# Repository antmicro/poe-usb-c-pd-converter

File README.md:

# Power over Ethernet to USB-C Power Delivery Adapter 

Copyright (c) 2024-2025 [Antmicro](https://www.antmicro.com)

## Overview

This project contains open hardware PCB design files for an adapter that splits a Power-over-Ethernet (PoE) capable RJ45 interface port into a USB-C Power Delivery (PD) port and an Ethernet RJ45 port. 
It negotiates power from PoE Power Sourcing Equipment (PSE) such as a PoE switch or a PoE injector.
For the USB-C connection, the board serves as an Upstream Facing Port (UFP) power source.
The USB-C port can be used for reading current and voltage negotiated for the PD.

## Key features

* RJ45 input port for data and PoE++ (IEEE 802.3bt)
* RJ45 output port passing raw Ethernet data from the input port
* USB-C regular connector with Power Delivery feature and USB data downstream
* Automatic input power negotiation (up to 71W) from PSE
* Externally programmable flash memory
* Programmable USB Power Delivery power profiles up to 60W
* On-board VBUS voltage, current and power measurement circuitry
* On-board external fan driver with a 4-pin standard receptacle
* 112 x 56 mm (4.4 x 2.2 inch) mechanical outline

## Project structure

The main directory contains KiCad PCB design files, a LICENSE and a README.
The remaining files are stored in the following directories:
* `img` - contains graphics for this README

## License
 
This project is published under the [Apache-2.0](LICENSE) license.

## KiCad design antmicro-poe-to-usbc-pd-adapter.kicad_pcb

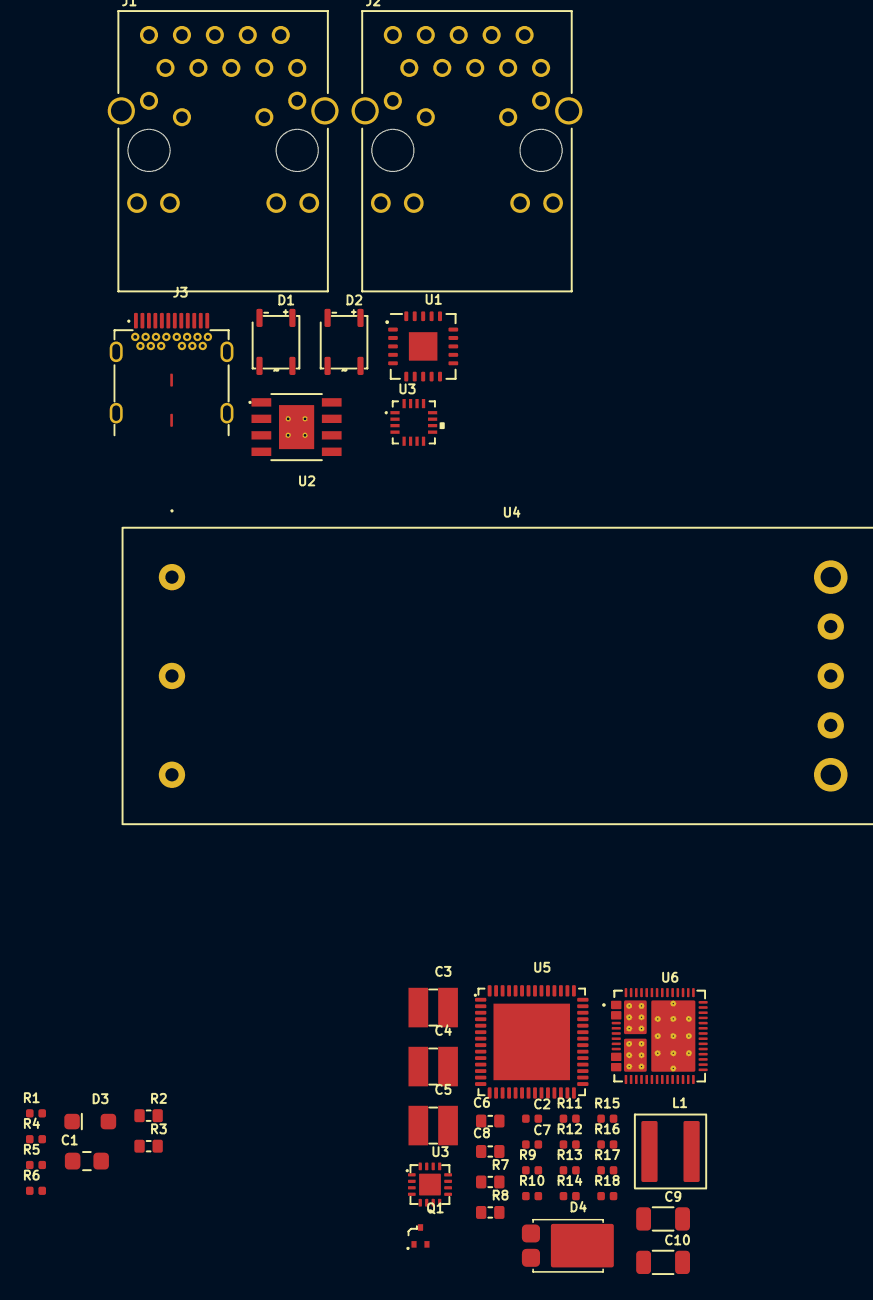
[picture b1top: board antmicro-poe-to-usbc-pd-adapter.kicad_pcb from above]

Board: 2 copper layers, 44 parts (0 on the bottom side), 49 nets, no tracks yet.

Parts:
C1: C_100n_100V_0805; C_0805_2012Metric
C2: C_10n_50V_X7R_0402; C_0402_1005Metric
C3: C_4u7_1210_100V; C_1210_3225Metric
C4, C5: C_2u2_1210; C_1210_3225Metric
C6, C8: C_100n_100V_X7R_0603; C_0603_1608Metric
C7: C_3n3_0402; C_0402_1005Metric
C9, C10: C_47u_25V_1206; C_1206_3216Metric
D1, D2: CD-MMBL110S; DFN3538
D3: PTVS58VS1UR,115; D_SOD-123F
D4: PDS760; PowerDI5
J1, J2: Bus_RJ45_5-2337992-8; RJ45_X-2337992-8_Horizontal
J3: USB-C_WE_632723300011; USB-C_Receptacle_WE_632723300011
L1: L_6u8_6.1A_MPS-MPL-AL5050; L_MPS-MPL-AL5050
Q1: PJE138K; SOT-523
R1: R_24k9_0402; R_0402_1005Metric
R2: R_63R4_0603; R_0603_1608Metric
R3: R_90R9_0603; R_0603_1608Metric
R4: R_1k3_0402; R_0402_1005Metric
R5: R_0R_0402; R_0402_1005Metric
R6: R_49k9_0402; R_0402_1005Metric
R7, R8: R_0R_0603; R_0603_1608Metric
R9: R_27k_0402; R_0402_1005Metric
R10: R_470k_0402; R_0402_1005Metric
R11: R_100k_0402; R_0402_1005Metric
R12: R_10k_0402; R_0402_1005Metric
R13: R_200k_0402; R_0402_1005Metric
R14: R_7k68_0402; R_0402_1005Metric
R15, R16: R_2k7_0402; R_0402_1005Metric
R17: R_4k7_0402; R_0402_1005Metric
R18: R_17k4_0402; R_0402_1005Metric
U1: TPS2372-3RGWR; VQFN-20_5x5x1mm_P0.65mm
U2: LV14540DDAR; SOIC-8-1EP_3.9x4.9x1.75mm_P1.27mm_EP_vias
U3: INA230AIRGTR; VQFN-16-1EP_3x3mm_P0.5mm_EP1.68x1.68mm
U3#2: STUSB4710AQ1TR; QFN-16_3x3mm_P0.5mm
U4: IEA48003A280V-001-R
U5: FT4232H_VQFN; QFN-56-1EP_8x8mm_P0.5mm
U6: TPS65988DHRSHR; IC_TPS65987DDHRSHR

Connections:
/CLSA: R2.2, U1.3 (CLSA)
/CLSB: R3.2, U1.6 (CLSB)
/P1: J1.1, J2.1
/P2: J1.2, J2.2
/P3: J1.3, J2.3
/P4: J1.4, J2.4
/P5: J1.5, J2.5
/P6: J1.6, J2.6
/P7: J1.7, J2.7
/P8: J1.8, J2.8
/P9: J1.9, J2.9
/P10: J1.10, J2.10
/POE.VC1: D1.3, J1.11 (VC1)
/POE.VC2: D1.4, J1.12 (VC2)
/POE.VC3: D2.4, J1.13 (VC3)
/POE.VC4: D2.3, J1.14 (VC4)
/VDD: C1.2, D1.2, D2.2, R1.1, R10.2, U1.1 (VDD), U4.1 (VIN+)
/VSS: C1.1, D1.1, D2.1, R2.1, R3.1, R4.1, R5.2, R6.1, U1.4 (VSSA), U1.5 (VSSB)
GND: C2.1, C3.1, C4.1, C5.1, C6.1, C7.1, C9.1, C10.1, D4.2 (A), R8.1, R9.1, R18.1, U2.7 (GND), U2.9 (GND), U4.4 (VOUT-), U4.5 (SENSE-)
GNDD: Q1.2 (S), R11.1, U1.11 (RTNA), U1.12 (RTNB), U4.3 (VIN-)
unnamed: C9.2, C10.2, L1.2, R13.2
unnamed: C8.1, D4.1 (C), L1.1, U2.8 (SW)
unnamed: J1.19 (SHIELD), J1.20 (SHIELD)
unnamed: J2.19 (SHIELD), J2.20 (SHIELD)
unnamed: J3.A1 (GND), J3.A12 (GND), J3.B1 (GND), J3.B12 (GND)
unnamed: Q1.3 (D), U4.2 (!ON)
unnamed: Q1.1 (G), R10.1, R11.2, R12.1
unnamed: R14.1, R15.2
unnamed: R15.1, R16.2
unnamed: R16.1, R17.2
unnamed: R17.1, R18.2
unnamed: R4.2, U1.8 (AMPS_CTL)
unnamed: R1.2, U1.2 (DEN)
unnamed: R5.1, U1.9 (MPS_DUTY)
unnamed: R12.2, U1.13 (PG)
unnamed: R6.2, U1.7 (REF)
unnamed: C8.2, U2.1 (BOOT)
unnamed: C3.2, C4.2, C5.2, C6.2, R7.1, U2.2 (VIN), U2.3 (EN), U4.7 (SENSE+), U4.8 (VOUT+)
unnamed: R13.1, R14.2, U2.5 (FB)
unnamed: R9.2, U2.4 (RT)
unnamed: C7.2, U2.6 (SS)
unnamed: C2.2, R7.2, R8.2, U4.6 (TRIM)
unnamed: U5.21 (GND), U5.41 (GND), U5.45 (GND), U5.57 (GND)
unnamed: U5.16 (V_{CCIO}), U5.36 (V_{CCIO}), U5.50 (V_{CCIO})
unnamed: U5.2 (V_{CORE}), U5.31 (V_{CORE})
unnamed: U6.20 (GND), U6.51 (GND)
unnamed: U6.8 (DRAIN1), U6.15 (DRAIN1), U6.19 (DRAIN1), U6.58 (DRAIN1)
unnamed: U6.7 (DRAIN2), U6.52 (DRAIN2), U6.56 (DRAIN2), U6.57 (DRAIN2)
VBUS: J3.A4 (VBUS), J3.A9 (VBUS), J3.B4 (VBUS), J3.B9 (VBUS)

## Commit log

2025-12-30 Add LICENSE
2025-12-30 [#62182] Connect LV14540
2025-12-30 [#62182] Create schematic place components route TPS2372
2025-12-30 [#62182] Add shunt resistor for INA230
2025-12-30 [#62623] Add planes to variable buck
2025-12-30 [#62182] Change passives, correct gnd
2025-12-30 [#62623] Improved schematic, added hierarchy
2025-12-30 [#62623] Improve schematic, change 3V3 buck inductor, correct SPI, add testpoint
2025-12-30 [#62182] Add INA230, remove STUSB4710
2025-12-30 [#62623] Las commit before major change in placement
2025-12-30 [#62182] Major changes in schematic
    Add TPS65987D
    Add FT4232H
    Add 3v3 buck
    Connect components
2025-12-30 [#62182] Update resistor fields
2025-12-30 [#62182] Place components PCB
2025-12-30 [#62623] Change hierarchy implementation
2025-12-30 [#62182] Connect INA230
    This is first commit after Meeting #62027
2025-12-30 [#62182] Update stackup
2025-12-30 [#62182] Change R5
2025-12-30 [#62623] Minor changes in placement/schematic
2025-12-30 [#62182] Tie VBUS1 and VBUS2
2025-12-30 [#62182] Add mux to flash
2025-12-30 [#62623] PCB initial placement
2025-12-30 [#62182] Add logo, add mountin holes
2025-12-30 [#62623] Minor graphical changes
2025-12-30 [#62182] Clean schematic
2025-12-30 [#62835] Route ETH differential pairs
2025-12-30 [#62835] Change dcdc placement, change IC's placement
2025-12-30 [#62835] Change R30 to geneerate CI
2025-12-30 [#62835] Start PWR plane placement
2025-12-30 [#62835] Create WRL
2025-12-30 [#62835] PoE to USB-C PD Review Rev.1.0.0 correct points 1,3,4,6,7,11
2025-12-30 [#62835] Finish routing, start silcscreen
2025-12-30 [#62835] Improve EHT tuning
2025-12-30 [#62835] Add filtering capacitors to FTDI
2025-12-30 [#62835] Add switch explanation
2025-12-30 [#62835] Add esd protection for usb, add pwr planes, route LS signals
2025-12-30 [#62835] Add 3V3 LDO
2025-12-30 [#62835] Tackle DRC problems, change vias size
2025-12-30 [#62835] Tune ETH length
2025-12-30 [#62835] Correct OSHW-logo
2025-12-30 [#62835] Add ETH receptacle diode steering
2025-12-30 [#62835] Start routing low speed signals
2025-12-30 [#62835] Add vias, second GND plane, GNDD plane, lower INA IC, minor changes
2025-12-30 [#62835] Finish silcscreen reference values placement
2025-12-30 [#62835] Tacle ERC problems, add PWR flags
2025-12-30 [#62835] Add place for SHA
2025-12-30 [#62835] Add 3V3 LDO to PCB, place CBUS capacitors, change 5V buck layout
2025-12-30 [#62835] Change L3 3V3 buck and divider, to 5V dcdc buck
2025-12-30 [#63274] Add status LEDs for PoE controller
2025-12-30 [#62835] Change IEA48003A280V-001-R input capacitors
2025-12-30 [#63274] Imported WRL, prepare for visualisation
2025-12-30 [#63274] Change sha for ########
2025-12-30 [#63274] Add heatsink, clear DRC
2025-12-30 [#62835] Change planes below IEA4800(..), place capacitors
2025-12-30 [#63274] Add testpoints, improve silcscreen
2025-12-30 [#63274] Add PSE type marking
2025-12-30 [#63274] Change switch description
2025-12-30 [#63274] Connect 5V trace to FTDI
2025-12-30 [#63274] Moved DCDC, placed heatsink
2025-12-30 [#63274] Add vias for DCDC cooling
2025-12-30 [#63274] Change TPS65987 feedback for DCDC gpio pinout
2025-12-30 [#62835] Routed tracks to ethernet receptacle LED
2025-12-30 [#63274] Add heatsink, start moving components to make space
2025-12-30 [#63274] Add planes for TPS65987 cooling
2025-12-30 [#63274] Clean repository
2025-12-30 [#63274] Change transistors to BS5123
2025-12-30 [#63274] Prepare for visualization and fabhouse
2025-12-30 [#63274] Add optocouplers for ETH diode, TPS65987D HRESET
2025-12-30 [#63274] Remove one optocoupler, add components to PCB, route PCB
2025-12-30 [#63274] Update R28 and R31
2025-12-30 [#63274] Update symbol R79 and R10 for CI
2025-12-30 [#63798] Change via position
2025-12-30 [#62182] Update .gitignore, remove tmp files
2025-12-30 [#63798] Change SOIC-8-1EP_3.9x4.9x1.75mm_P1.27mm for the same one but without EP
2025-12-30 [#63274] Again change R10
2025-12-30 [#63274] Placed transistors on PCB, routed, cleared DRC
2025-12-30 [#63274] Generate visualisation
2025-12-30 [#64013] Prepare production fixes
2025-12-30 Add README
2025-12-30 [#64111] Change sheet enumeration
2025-12-30 [#63274] Change vias to 0.55 / 0.2 and solve drcs
2025-12-30 [#64111] Got rid of redundant labels
2025-12-30 [#66725] Implement changes from review for rev 1.1.0
2025-12-30 [#63068] Regenerate schematic pdf
2025-12-30 [#63274] override U6 via settings
2025-12-30 [#63068] Fix readme mistakes, change img to assets folder
2025-12-30 Add CI, cleanup assets
2025-12-30 Bump to KiCad9
2025-12-30 Bump release date, unify naming
2025-12-30 Remove redundant assets
2025-12-30 Cleanup
2025-12-30 README review

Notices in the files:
parts and their libraries:
License: Apache-2.0
